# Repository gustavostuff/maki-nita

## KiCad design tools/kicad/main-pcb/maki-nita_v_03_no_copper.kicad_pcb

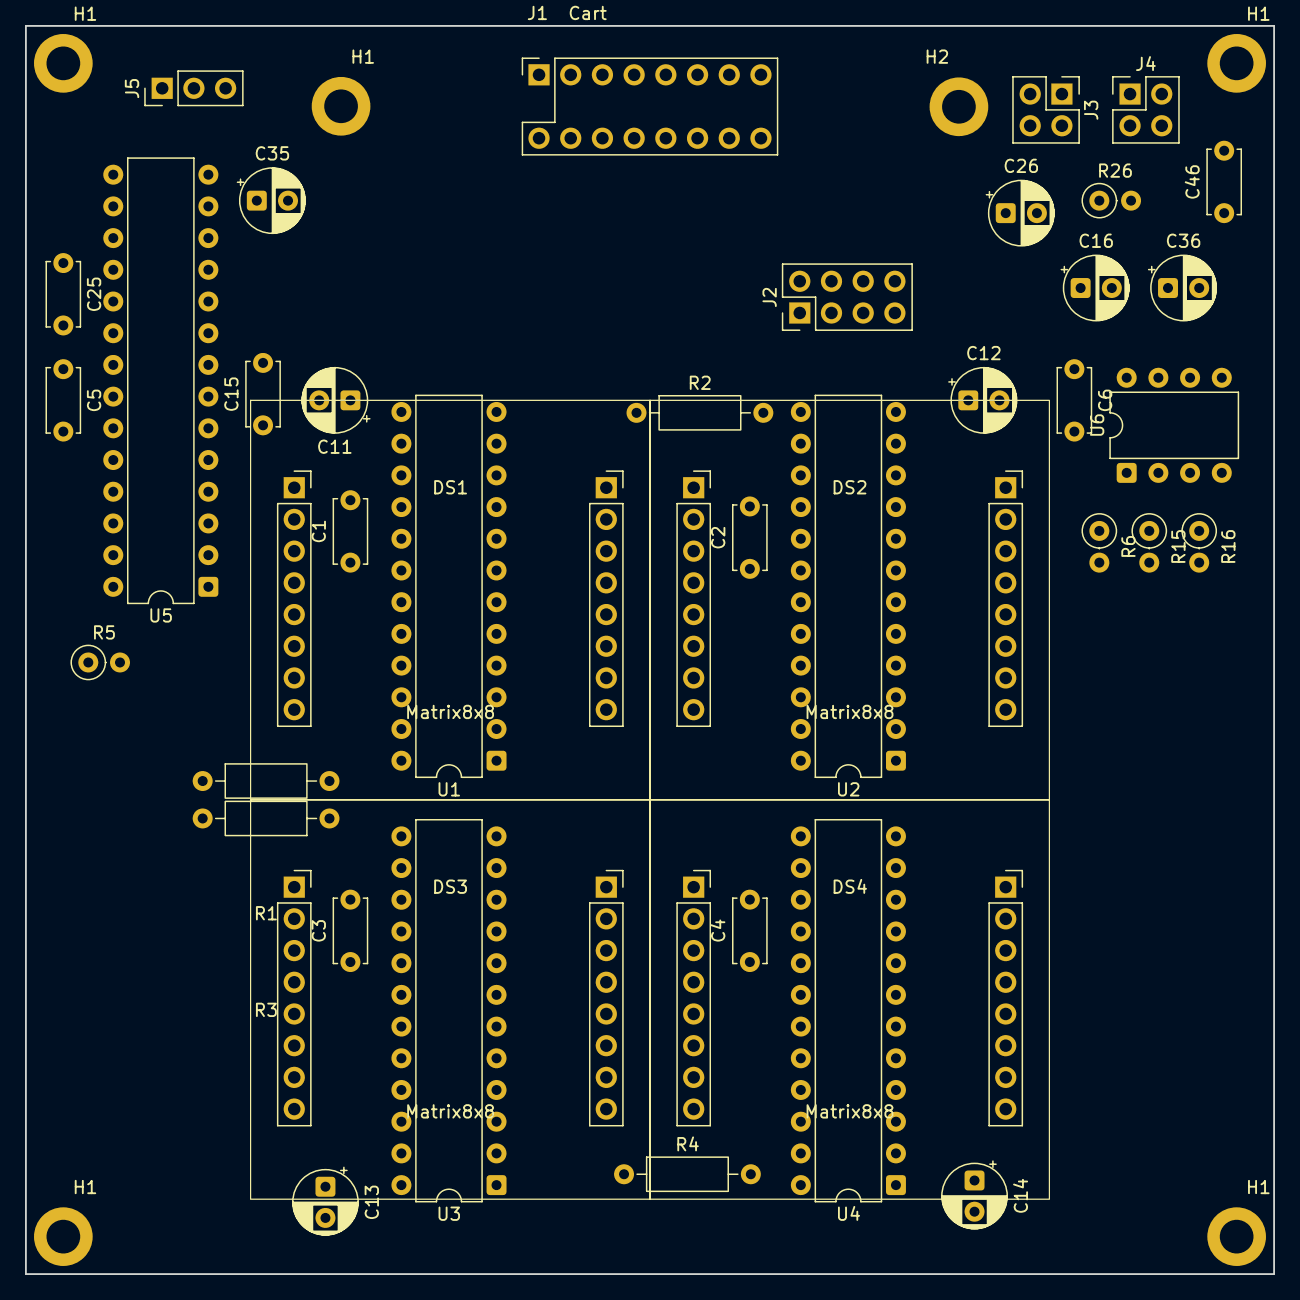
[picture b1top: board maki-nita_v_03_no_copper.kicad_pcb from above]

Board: 2 copper layers, 100.0 x 100.0 mm, 47 parts (0 on the bottom side), 91 nets, no tracks yet.

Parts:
C1: U1 V+; C_Disc_D5.0mm_W2.5mm_P5.00mm
C2: U2 V+; C_Disc_D5.0mm_W2.5mm_P5.00mm
C3: U3 V+; C_Disc_D5.0mm_W2.5mm_P5.00mm
C4: U4 V+; C_Disc_D5.0mm_W2.5mm_P5.00mm
C5: U5 VDD; C_Disc_D5.0mm_W2.5mm_P5.00mm
C6: U6 VS; C_Disc_D5.0mm_W2.5mm_P5.00mm
C11: U1 10u; CP_Radial_D5.0mm_P2.50mm
C12: U2 10u; CP_Radial_D5.0mm_P2.50mm
C13: U3 10u; CP_Radial_D5.0mm_P2.50mm
C14: U4 10u; CP_Radial_D5.0mm_P2.50mm
C15: U5 AVDD; C_Disc_D5.0mm_W2.5mm_P5.00mm
C16: U6 VS; CP_Radial_D5.0mm_P2.50mm
C25: U5 IO; C_Disc_D5.0mm_W2.5mm_P5.00mm
C26: U6 BYP; CP_Radial_D5.0mm_P2.50mm
C35: 1u DAC; CP_Radial_D5.0mm_P2.50mm
C36: 220u SPK; CP_Radial_D5.0mm_P2.50mm
C46: 47n ZOB; C_Disc_D5.0mm_W2.5mm_P5.00mm
DS1, DS2, DS3, DS4: Matrix8x8; Matrix8x8_2x8_P2.52mm_R25mm
H1, H1#2, H1#3, H1#4, H1#5, H2: MountingHole_2.7mm_M2.5_DIN965_Pad
J1: Cart; EDAC_345_MoboSocket_2x8_2.54x5.08mm
J2: Controls; PinHeader_2x04_P2.54mm_Vertical
J3: Power; PinHeader_2x02_P2.54mm_Vertical
J4: Speaker; PinHeader_2x02_P2.54mm_Vertical
J5: UPDI; PinHeader_1x03_P2.54mm_Vertical
R1: U1 ISET; R_Axial_DIN0207_L6.3mm_D2.5mm_P10.16mm_Horizontal
R2: U2 ISET; R_Axial_DIN0207_L6.3mm_D2.5mm_P10.16mm_Horizontal
R3: U3 ISET; R_Axial_DIN0207_L6.3mm_D2.5mm_P10.16mm_Horizontal
R4: U4 ISET; R_Axial_DIN0207_L6.3mm_D2.5mm_P10.16mm_Horizontal
R5: 10k EVENT; R_Axial_DIN0207_L6.3mm_D2.5mm_P2.54mm_Vertical
R6: 22k IN; R_Axial_DIN0207_L6.3mm_D2.5mm_P2.54mm_Vertical
R15: 10k DAC; R_Axial_DIN0207_L6.3mm_D2.5mm_P2.54mm_Vertical
R16: 1k IN; R_Axial_DIN0207_L6.3mm_D2.5mm_P2.54mm_Vertical
R26: 10R ZOB; R_Axial_DIN0207_L6.3mm_D2.5mm_P2.54mm_Vertical
U1, U2, U3, U4: MAX7219; DIP-24_W7.62mm
U5: Audio AVR; DIP-28_W7.62mm
U6: LM386; DIP-8_W7.62mm

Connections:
+5V: C1.1, C2.1, C3.1, C4.1, C5.1, C6.1, C11.1, C12.1, C13.1, C14.1, C15.1, C16.1, C25.1, J1.3, J1.4, J1.16, J2.2, J3.2, J5.2, R1.1, R2.1, R3.1, R4.1, R5.2, U1.19, U2.19, U3.19, U4.19, U5.6, U5.14, U5.20, U6.6
AMP: C36.1, R26.1, U6.5
AUD: C35.2, R6.1
AUDIN: R6.2, R16.1, U6.3
AUDIO_UPDI: J5.1, U5.19
BUTTON: J1.13, J2.7
BYPASS: C26.1, U6.7
CLK: J1.10, U1.13, U2.13, U3.13, U4.13
DAC: C35.1, R15.1, U5.12
DIN: J1.8, U1.1
DOUT_U1: U1.24, U2.1
DOUT_U2: U2.24, U3.1
DOUT_U3: U3.24, U4.1
DOWN: J1.7, J2.4
DS1_C0: DS1.1, U1.22
DS1_C1: DS1.2, U1.14
DS1_C2: DS1.3, U1.16
DS1_C3: DS1.4, U1.20
DS1_C4: DS1.5, U1.23
DS1_C5: DS1.6, U1.21
DS1_C6: DS1.7, U1.15
DS1_C7: DS1.8, U1.17
DS1_R0: DS1.16, U1.2
DS1_R1: DS1.15, U1.11
DS1_R2: DS1.14, U1.6
DS1_R3: DS1.13, U1.7
DS1_R4: DS1.12, U1.3
DS1_R5: DS1.11, U1.10
DS1_R6: DS1.10, U1.5
DS1_R7: DS1.9, U1.8
DS2_C0: DS2.1, U2.22
DS2_C1: DS2.2, U2.14
DS2_C2: DS2.3, U2.16
DS2_C3: DS2.4, U2.20
DS2_C4: DS2.5, U2.23
DS2_C5: DS2.6, U2.21
DS2_C6: DS2.7, U2.15
DS2_C7: DS2.8, U2.17
DS2_R0: DS2.16, U2.2
DS2_R1: DS2.15, U2.11
DS2_R2: DS2.14, U2.6
DS2_R3: DS2.13, U2.7
DS2_R4: DS2.12, U2.3
DS2_R5: DS2.11, U2.10
DS2_R6: DS2.10, U2.5
DS2_R7: DS2.9, U2.8
DS3_C0: DS3.1, U3.22
DS3_C1: DS3.2, U3.14
DS3_C2: DS3.3, U3.16
DS3_C3: DS3.4, U3.20
DS3_C4: DS3.5, U3.23
DS3_C5: DS3.6, U3.21
DS3_C6: DS3.7, U3.15
DS3_C7: DS3.8, U3.17
DS3_R0: DS3.16, U3.2
DS3_R1: DS3.15, U3.11
DS3_R2: DS3.14, U3.6
DS3_R3: DS3.13, U3.7
DS3_R4: DS3.12, U3.3
DS3_R5: DS3.11, U3.10
DS3_R6: DS3.10, U3.5
DS3_R7: DS3.9, U3.8
DS4_C0: DS4.1, U4.22
DS4_C1: DS4.2, U4.14
DS4_C2: DS4.3, U4.16
DS4_C3: DS4.4, U4.20
DS4_C4: DS4.5, U4.23
DS4_C5: DS4.6, U4.21
DS4_C6: DS4.7, U4.15
DS4_C7: DS4.8, U4.17
DS4_R0: DS4.16, U4.2
DS4_R1: DS4.15, U4.11
DS4_R2: DS4.14, U4.6
DS4_R3: DS4.13, U4.7
DS4_R4: DS4.12, U4.3
DS4_R5: DS4.11, U4.10
DS4_R6: DS4.10, U4.5
DS4_R7: DS4.9, U4.8
EVENT: J1.2, R5.1, U5.23
GND: C1.2, C2.2, C3.2, C4.2, C5.2, C6.2, C11.2, C12.2, C13.2, C14.2, C15.2, C16.2, C25.2, C26.2, C46.2, J1.1, J1.15, J2.1, J2.8, J3.1, J3.4, J4.1, J4.4, J5.3, R15.2, R16.2, U1.4, U1.9, U2.4, U2.9, U3.4, U3.9, U4.4, U4.9, U5.15, U5.21, U6.2, U6.4
LEFT: J1.9, J2.5
LOAD: J1.6, U1.12, U2.12, U3.12, U4.12
RESET: J1.12, J3.3, U5.18
RIGHT: J1.11, J2.6
SPK: C36.2, J4.2, J4.3
U1_ISET: R1.2, U1.18
U2_ISET: R2.2, U2.18
U3_ISET: R3.2, U3.18
U4_ISET: R4.2, U4.18
UP: J1.5, J2.3
ZOBEL: C46.1, R26.2

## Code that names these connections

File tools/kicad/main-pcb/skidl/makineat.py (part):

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audio AVR and U6 is the LM386. U1 to U4 are the MAX7219 chain, left to
right, top to bottom. DS1 to DS4 are the matrices those drivers scan.
The sim keeps the picture inside each driver. It models the audio AVR
on EVENT, and it models J5. Here each segment and digit pin lands on
one matrix pad.

A part that sits on Un uses n. A second part on that IC adds 10, a
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    (2, "VCC"),
)

# 1x2 speaker header (Pin 1 is GND, Pin 2 is SPK).
SPK_PINS = (
    (1, "GND"),
    (2, "SPK"),
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    (24, "DOUT"),
)

# Same 28-pin map as the cartridge. PD6 is the DAC. PA1 listens to EVENT.
AUDIO_PINS = (
    (1, "PA7"),
    (2, "PC0"),
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    _tie(shunt, 1, audin)
    _tie(shunt, 2, gnd)

    amp = _part("LM386N-1", "U6", AMP_FP, AMP_PINS, "LM386", "LM386N-1 speaker amplifier")
    _tie(amp, 2, gnd)
    _tie(amp, 3, audin)
    _tie(amp, 4, gnd)
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    # Unused AVR pins and LM386 gain pins 1 and 8 stay open. Stub them
    # so every footprint pad has a pin in the netlist.
    _stub_unused(cpu, AUDIO_PINS)
    _stub_unused(amp, AMP_PINS)


def build() -> None:
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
